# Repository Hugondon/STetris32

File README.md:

# STetris32
My version of the famous game "Tetris" using a system based on the Blue Pill dev board.
## Information
The sole purpose of this project is to recreate the game mechanics and introduce some other different features regarding in-game audio :). 
## Block Diagram

The system can be summarized in three big modules:
1. Game Display Module.
    - SPI communication with MAX7219 to control two 8x8 LED matrices.
    - I2C communication with SSD1306 OLED Driver connected to 128x64 dot display to show the player's score and the current song being played.
2. Sound Module.
    - PWM + NPN BJT circuit driven 4 ohm speakers.
3. User Interface Module.
    - 6 buttons with different functionalities (up/down/left/right/center/reset).
## Schematic
The connections the user must make are the following:

## Video

Pending upload.

## Useful Information
- [OLED Display](https://controllerstech.com/oled-display-using-i2c-stm32/)
- [Matrices](https://acoptex.com/project/160/basics-project-032a-8x8-dot-led-matrix-64-led-digital-display-common-anode-and-common-cathode-at-lex-c/)

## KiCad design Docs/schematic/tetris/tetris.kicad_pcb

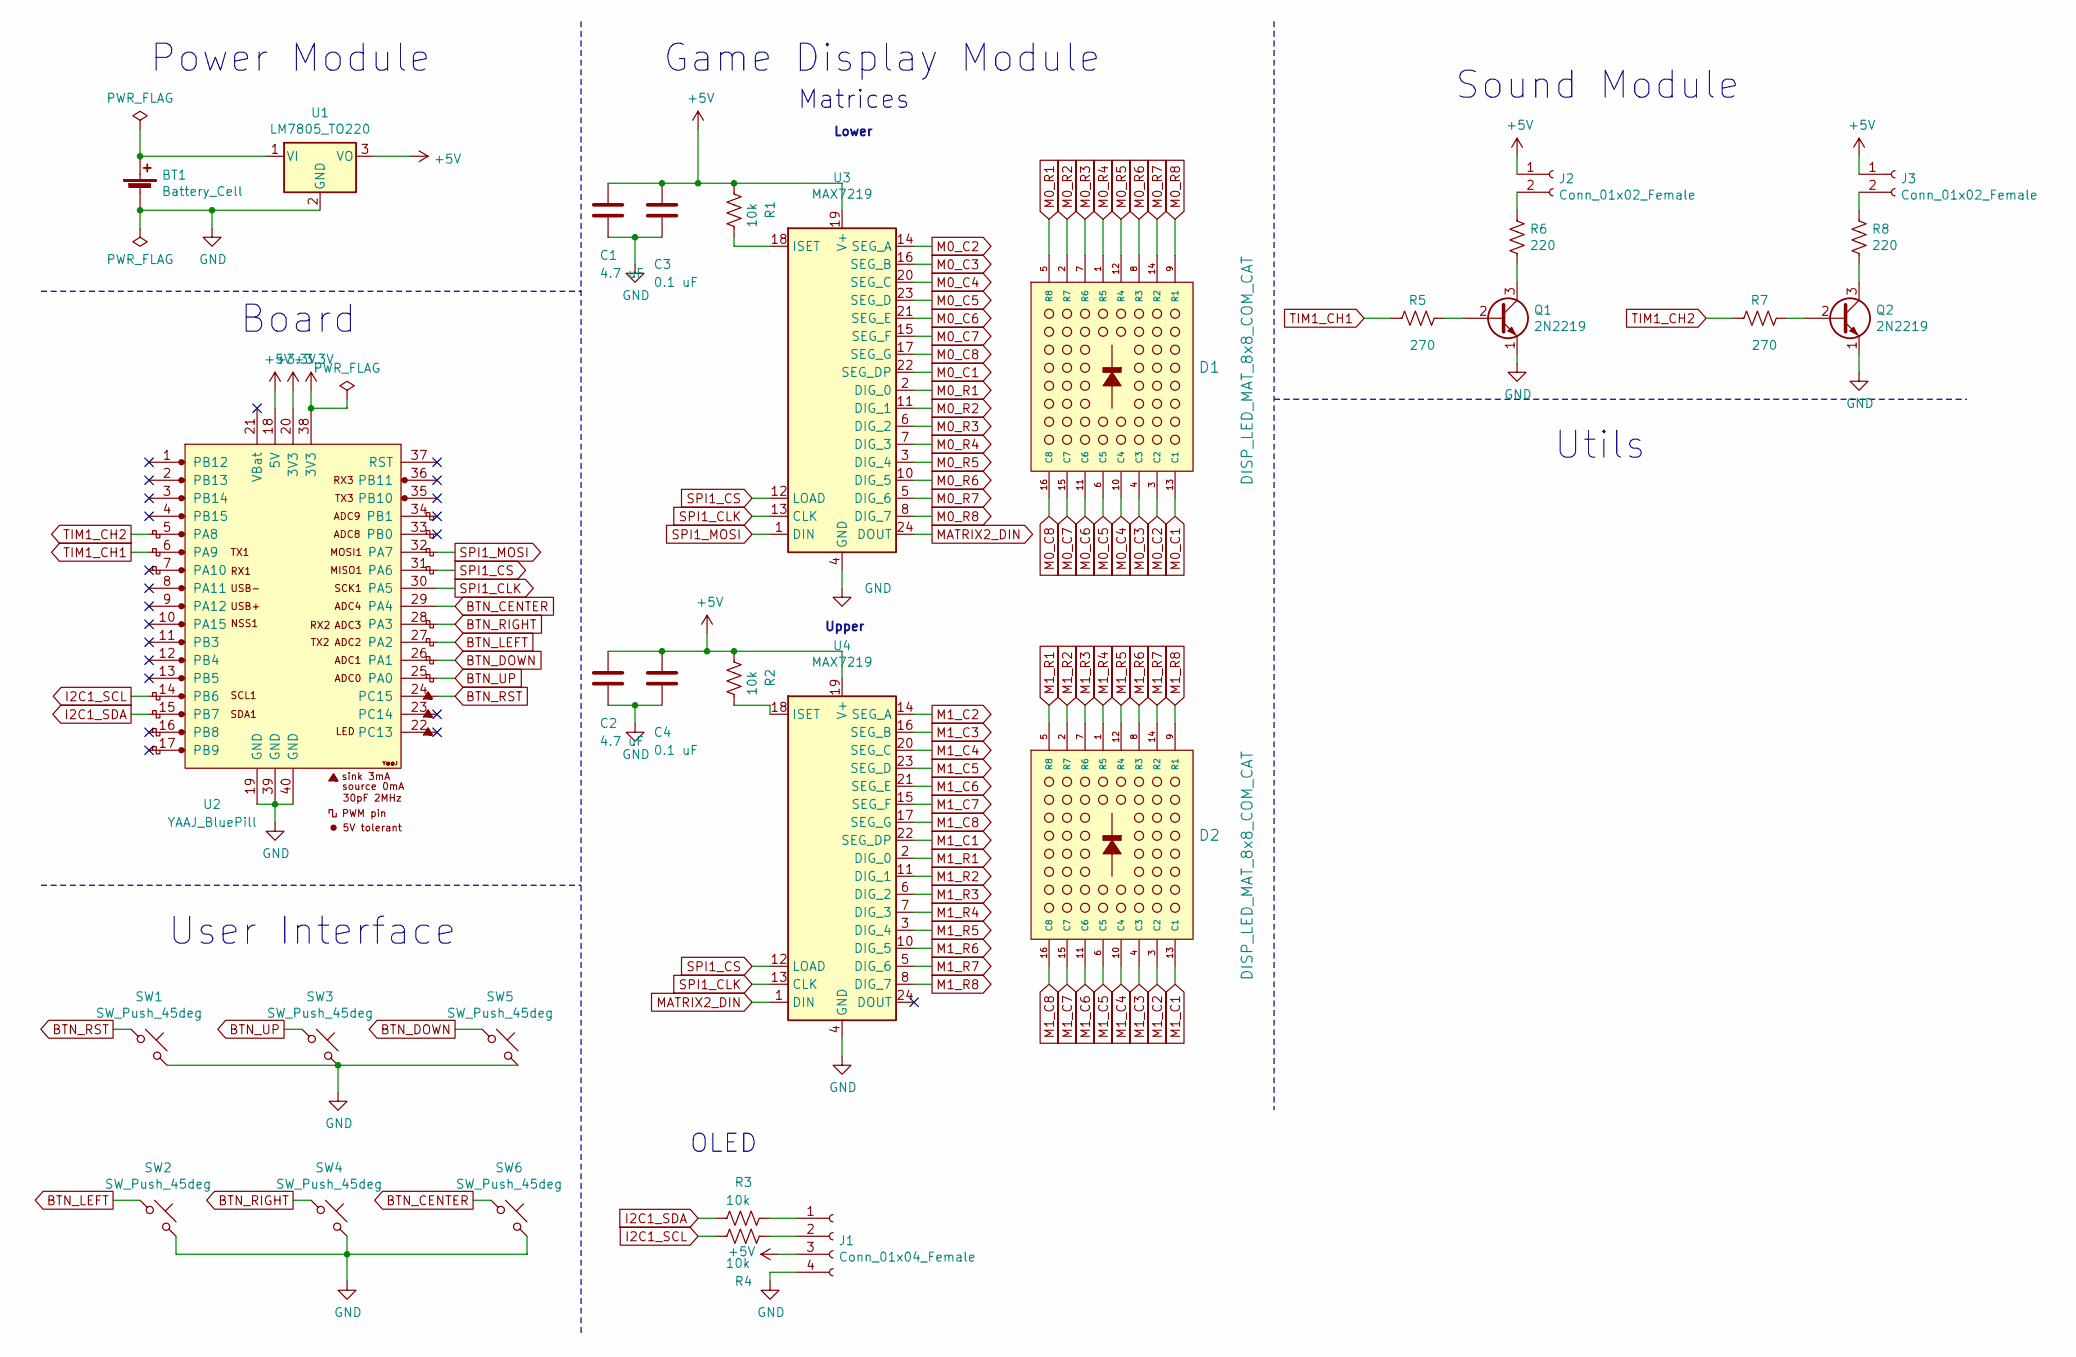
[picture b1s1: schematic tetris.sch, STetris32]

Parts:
BT1: Battery_Cell; BatteryHolder_MPD_BA9VPC_1xPP3
C1, C2: 4.7 uF; C_0603_1608Metric
C3, C4: 0.1 uF; C_0603_1608Metric
D1, D2: DISP_LED_MAT_8x8_COM_CAT; LED_8x8_3MM_32x32MM
J1: Conn_01x04_Female; PinHeader_1x04_P2.54mm_Vertical
J2, J3: Conn_01x02_Female; PinHeader_1x02_P2.54mm_Vertical
Q1, Q2: 2N2219; TO-92
R1, R2, R3, R4: 10k; R_0603_1608Metric
R5, R7: 270; R_0603_1608Metric
R6, R8: 220; R_0603_1608Metric
SW1, SW2, SW3, SW4, SW5, SW6: SW_Push_45deg; SW_PUSH-12mm
U1: LM7805_TO220; TO-220-3_Vertical
U2: YAAJ_BluePill; YAAJ_BluePill_1
U3, U4: MAX7219; DIP-24_W7.62mm

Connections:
+3V3: U2.20 (3V3), U2.38 (3V3)
+5V: C1.1, C2.1, C3.1, C4.1, J1.3, J2.1, J3.1, R1.1, R2.1, U1.3 (VO), U2.18 (5V), U3.19 (V+), U4.19 (V+)
BTN_CENTER: SW6.1, U2.29 (PA4)
BTN_DOWN: SW5.1, U2.26 (PA1)
BTN_LEFT: SW2.1, U2.27 (PA2)
BTN_RIGHT: SW4.1, U2.28 (PA3)
BTN_RST: SW1.1, U2.24 (PC15)
BTN_UP: SW3.1, U2.25 (PA0)
GND: BT1.2 (-), C1.2, C2.2, C3.2, C4.2, J1.4, Q1.1 (E), Q2.1 (E), SW1.2, SW2.2, SW3.2, SW4.2, SW5.2, SW6.2, U1.2 (GND), U2.19 (GND), U2.39 (GND), U2.40 (GND), U3.4 (GND), U3.9 (GND), U4.4 (GND), U4.9 (GND)
I2C1_SCL: R4.2, U2.14 (PB6)
I2C1_SDA: R3.2, U2.15 (PB7)
M0_C1: D1.13 (C1), U3.22 (SEG_DP)
M0_C2: D1.3 (C2), U3.14 (SEG_A)
M0_C3: D1.4 (C3), U3.16 (SEG_B)
M0_C4: D1.10 (C4), U3.20 (SEG_C)
M0_C5: D1.6 (C5), U3.23 (SEG_D)
M0_C6: D1.11 (C6), U3.21 (SEG_E)
M0_C7: D1.15 (C7), U3.15 (SEG_F)
M0_C8: D1.16 (C8), U3.17 (SEG_G)
M0_R1: D1.5 (R8), U3.2 (DIG_0)
M0_R2: D1.2 (R7), U3.11 (DIG_1)
M0_R3: D1.7 (R6), U3.6 (DIG_2)
M0_R4: D1.1 (R5), U3.7 (DIG_3)
M0_R5: D1.12 (R4), U3.3 (DIG_4)
M0_R6: D1.8 (R3), U3.10 (DIG_5)
M0_R7: D1.14 (R2), U3.5 (DIG_6)
M0_R8: D1.9 (R1), U3.8 (DIG_7)
M1_C1: D2.13 (C1), U4.22 (SEG_DP)
M1_C2: D2.3 (C2), U4.14 (SEG_A)
M1_C3: D2.4 (C3), U4.16 (SEG_B)
M1_C4: D2.10 (C4), U4.20 (SEG_C)
M1_C5: D2.6 (C5), U4.23 (SEG_D)
M1_C6: D2.11 (C6), U4.21 (SEG_E)
M1_C7: D2.15 (C7), U4.15 (SEG_F)
M1_C8: D2.16 (C8), U4.17 (SEG_G)
M1_R1: D2.5 (R8), U4.2 (DIG_0)
M1_R2: D2.2 (R7), U4.11 (DIG_1)
M1_R3: D2.7 (R6), U4.6 (DIG_2)
M1_R4: D2.1 (R5), U4.7 (DIG_3)
M1_R5: D2.12 (R4), U4.3 (DIG_4)
M1_R6: D2.8 (R3), U4.10 (DIG_5)
M1_R7: D2.14 (R2), U4.5 (DIG_6)
M1_R8: D2.9 (R1), U4.8 (DIG_7)
MATRIX2_DIN: U3.24 (DOUT), U4.1 (DIN)
unnamed: BT1.1 (+), U1.1 (VI)
unnamed: J1.1, R3.1
unnamed: J1.2, R4.1
unnamed: J2.2, R6.1
unnamed: J3.2, R8.1
unnamed: Q1.2 (B), R5.2
unnamed: Q1.3 (C), R6.2
unnamed: Q2.2 (B), R7.2
unnamed: Q2.3 (C), R8.2
unnamed: R1.2, U3.18 (ISET)
unnamed: R2.2, U4.18 (ISET)
SPI1_CLK: U2.30 (PA5), U3.13 (CLK), U4.13 (CLK)
SPI1_CS: U2.31 (PA6), U3.12 (LOAD), U4.12 (LOAD)
SPI1_MOSI: U2.32 (PA7), U3.1 (DIN)
TIM1_CH1: R5.1, U2.6 (PA9)
TIM1_CH2: R7.1, U2.5 (PA8)

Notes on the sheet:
Power Module
Board
User Interface
Game Display Module
Sound Module
Matrices
OLED
Utils
Lower
Upper

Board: 2 copper layers, 30 parts (0 on the bottom side), 60 nets, no tracks yet.

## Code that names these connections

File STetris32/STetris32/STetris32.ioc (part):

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Mcu.Name=STM32F103C(8-B)Tx
Mcu.Package=LQFP48
Mcu.UserName=STM32F103C8Tx
PA0-WKUP.GPIOParameters=GPIO_PuPd,GPIO_Label,GPIO_ModeDefaultEXTI
PA0-WKUP.GPIO_Label=BTN_UP
PA0-WKUP.GPIO_ModeDefaultEXTI=GPIO_MODE_IT_FALLING
PA0-WKUP.GPIO_PuPd=GPIO_PULLUP
PA0-WKUP.Signal=GPXTI0
PA1.GPIOParameters=GPIO_PuPd,GPIO_Label,GPIO_ModeDefaultEXTI
PA1.GPIO_Label=BTN_DOWN
PA1.GPIO_ModeDefaultEXTI=GPIO_MODE_IT_FALLING
PA1.GPIO_PuPd=GPIO_PULLUP
PA1.Signal=GPXTI1
PA13.Mode=Serial_Wire
PA13.Signal=SYS_JTMS-SWDIO
PA14.Mode=Serial_Wire
PA14.Signal=SYS_JTCK-SWCLK
PA2.GPIOParameters=GPIO_PuPd,GPIO_Label,GPIO_ModeDefaultEXTI
PA2.GPIO_Label=BTN_LEFT
PA2.GPIO_ModeDefaultEXTI=GPIO_MODE_IT_FALLING
PA2.GPIO_PuPd=GPIO_PULLUP
PA2.Signal=GPXTI2
PA3.GPIOParameters=GPIO_PuPd,GPIO_Label
PA3.GPIO_Label=BTN_RIGHT
PA3.GPIO_PuPd=GPIO_PULLUP
PA3.Signal=GPXTI3
PA4.GPIOParameters=GPIO_PuPd,GPIO_Label,GPIO_ModeDefaultEXTI
PA4.GPIO_Label=BTN_CENTER
PA4.GPIO_ModeDefaultEXTI=GPIO_MODE_IT_FALLING
PA4.GPIO_PuPd=GPIO_PULLUP
PA4.Signal=GPXTI4
PA5.Mode=TX_Only_Simplex_Unidirect_Master
PA5.Signal=SPI1_SCK
PA6.GPIOParameters=GPIO_Label
PA6.GPIO_Label=SPI1_CS
PA6.Signal=GPIO_Output
PA7.Mode=TX_Only_Simplex_Unidirect_Master
PA7.Signal=SPI1_MOSI
PA8.Signal=S_TIM1_CH1
PA9.Signal=S_TIM1_CH2
PB6.Mode=I2C
PB6.Signal=I2C1_SCL
PB7.Mode=I2C
PB7.Signal=I2C1_SDA
PC13-TAMPER-RTC.GPIOParameters=GPIO_Label
PC13-TAMPER-RTC.GPIO_Label=LED_BUILTIN
PC13-TAMPER-RTC.Signal=GPIO_Output
PC15-OSC32_OUT.GPIOParameters=GPIO_PuPd,GPIO_Label,GPIO_ModeDefaultEXTI
PC15-OSC32_OUT.GPIO_Label=BTN_RST
PC15-OSC32_OUT.GPIO_ModeDefaultEXTI=GPIO_MODE_IT_FALLING
PC15-OSC32_OUT.GPIO_PuPd=GPIO_PULLUP
PC15-OSC32_OUT.Signal=GPXTI15
PD0-OSC_IN.Mode=HSE-External-Oscillator
PD0-OSC_IN.Signal=RCC_OSC_IN
PD1-OSC_OUT.Mode=HSE-External-Oscillator
PD1-OSC_OUT.Signal=RCC_OSC_OUT
RCC.SYSCLKFreq_VALUE=16000000
RCC.SYSCLKSource=RCC_SYSCLKSOURCE_PLLCLK
board=custom

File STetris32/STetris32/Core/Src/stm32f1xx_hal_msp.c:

/* USER CODE BEGIN Header */
/**
  ******************************************************************************
  * File Name          : stm32f1xx_hal_msp.c
  * Description        : This file provides code for the MSP Initialization
  *                      and de-Initialization codes.
  ******************************************************************************
  * @attention
  *
  * <h2><center>&copy; Copyright (c) 2021 STMicroelectronics.
  * All rights reserved.</center></h2>
  *
  * This software component is licensed by ST under BSD 3-Clause license,
  * the "License"; You may not use this file except in compliance with the
  * License. You may obtain a copy of the License at:
  *                        opensource.org/licenses/BSD-3-Clause
  *
  ******************************************************************************
  */
/* USER CODE END Header */

/* Includes ------------------------------------------------------------------*/
#include "main.h"
/* USER CODE BEGIN Includes */

/* USER CODE END Includes */

/* Private typedef -----------------------------------------------------------*/
/* USER CODE BEGIN TD */

/* USER CODE END TD */

/* Private define ------------------------------------------------------------*/
/* USER CODE BEGIN Define */

/* USER CODE END Define */

/* Private macro -------------------------------------------------------------*/
/* USER CODE BEGIN Macro */

/* USER CODE END Macro */

/* Private variables ---------------------------------------------------------*/
/* USER CODE BEGIN PV */

/* USER CODE END PV */

/* Private function prototypes -----------------------------------------------*/
/* USER CODE BEGIN PFP */

/* USER CODE END PFP */

/* External functions --------------------------------------------------------*/
/* USER CODE BEGIN ExternalFunctions */

/* USER CODE END ExternalFunctions */

/* USER CODE BEGIN 0 */

/* USER CODE END 0 */

void HAL_TIM_MspPostInit(TIM_HandleTypeDef *htim);
                    /**
  * Initializes the Global MSP.
  */
void HAL_MspInit(void)
{
  /* USER CODE BEGIN MspInit 0 */

  /* USER CODE END MspInit 0 */

  __HAL_RCC_AFIO_CLK_ENABLE();
  __HAL_RCC_PWR_CLK_ENABLE();

  /* System interrupt init*/

  /** NOJTAG: JTAG-DP Disabled and SW-DP Enabled
  */
  __HAL_AFIO_REMAP_SWJ_NOJTAG();

  /* USER CODE BEGIN MspInit 1 */

  /* USER CODE END MspInit 1 */
}

/**
* @brief I2C MSP Initialization
* This function configures the hardware resources used in this example
* @param hi2c: I2C handle pointer
* @retval None
*/
void HAL_I2C_MspInit(I2C_HandleTypeDef* hi2c)
{
  GPIO_InitTypeDef GPIO_InitStruct = {0};
  if(hi2c->Instance==I2C1)
  {
  /* USER CODE BEGIN I2C1_MspInit 0 */

  /* USER CODE END I2C1_MspInit 0 */

    __HAL_RCC_GPIOB_CLK_ENABLE();
    /**I2C1 GPIO Configuration
    PB6     ------> I2C1_SCL
    PB7     ------> I2C1_SDA
    */
    GPIO_InitStruct.Pin = GPIO_PIN_6|GPIO_PIN_7;
    GPIO_InitStruct.Mode = GPIO_MODE_AF_OD;
    GPIO_InitStruct.Speed = GPIO_SPEED_FREQ_HIGH;
    HAL_GPIO_Init(GPIOB, &GPIO_InitStruct);

    /* Peripheral clock enable */
    __HAL_RCC_I2C1_CLK_ENABLE();
  /* USER CODE BEGIN I2C1_MspInit 1 */

  /* USER CODE END I2C1_MspInit 1 */
  }

}

/**
* @brief I2C MSP De-Initialization
* This function freeze the hardware resources used in this example
* @param hi2c: I2C handle pointer
* @retval None
*/
void HAL_I2C_MspDeInit(I2C_HandleTypeDef* hi2c)
{
  if(hi2c->Instance==I2C1)
  {
  /* USER CODE BEGIN I2C1_MspDeInit 0 */

  /* USER CODE END I2C1_MspDeInit 0 */
    /* Peripheral clock disable */
    __HAL_RCC_I2C1_CLK_DISABLE();

    /**I2C1 GPIO Configuration
    PB6     ------> I2C1_SCL
    PB7     ------> I2C1_SDA
    */
    HAL_GPIO_DeInit(GPIOB, GPIO_PIN_6);

    HAL_GPIO_DeInit(GPIOB, GPIO_PIN_7);

  /* USER CODE BEGIN I2C1_MspDeInit 1 */

  /* USER CODE END I2C1_MspDeInit 1 */
  }

}

/**
* @brief SPI MSP Initialization
* This function configures the hardware resources used in this example
* @param hspi: SPI handle pointer
* @retval None
*/
void HAL_SPI_MspInit(SPI_HandleTypeDef* hspi)
{
  GPIO_InitTypeDef GPIO_InitStruct = {0};
  if(hspi->Instance==SPI1)
  {
  /* USER CODE BEGIN SPI1_MspInit 0 */

  /* USER CODE END SPI1_MspInit 0 */
    /* Peripheral clock enable */
    __HAL_RCC_SPI1_CLK_ENABLE();

    __HAL_RCC_GPIOA_CLK_ENABLE();
    /**SPI1 GPIO Configuration
    PA5     ------> SPI1_SCK
    PA7     ------> SPI1_MOSI
    */
    GPIO_InitStruct.Pin = GPIO_PIN_5|GPIO_PIN_7;
    GPIO_InitStruct.Mode = GPIO_MODE_AF_PP;
    GPIO_InitStruct.Speed = GPIO_SPEED_FREQ_HIGH;
    HAL_GPIO_Init(GPIOA, &GPIO_InitStruct);

  /* USER CODE BEGIN SPI1_MspInit 1 */

  /* USER CODE END SPI1_MspInit 1 */
  }

}

/**
* @brief SPI MSP De-Initialization
* This function freeze the hardware resources used in this example
* @param hspi: SPI handle pointer
* @retval None
*/
void HAL_SPI_MspDeInit(SPI_HandleTypeDef* hspi)
{
  if(hspi->Instance==SPI1)
  {
  /* USER CODE BEGIN SPI1_MspDeInit 0 */

  /* USER CODE END SPI1_MspDeInit 0 */
    /* Peripheral clock disable */
    __HAL_RCC_SPI1_CLK_DISABLE();

    /**SPI1 GPIO Configuration
    PA5     ------> SPI1_SCK
    PA7     ------> SPI1_MOSI
    */
    HAL_GPIO_DeInit(GPIOA, GPIO_PIN_5|GPIO_PIN_7);

  /* USER CODE BEGIN SPI1_MspDeInit 1 */

  /* USER CODE END SPI1_MspDeInit 1 */
  }

}

/**
* @brief TIM_OC MSP Initialization
* This function configures the hardware resources used in this example
* @param htim_oc: TIM_OC handle pointer
* @retval None
*/
void HAL_TIM_OC_MspInit(TIM_HandleTypeDef* htim_oc)
{
  if(htim_oc->Instance==TIM1)
  {
  /* USER CODE BEGIN TIM1_MspInit 0 */

  /* USER CODE END TIM1_MspInit 0 */
    /* Peripheral clock enable */
    __HAL_RCC_TIM1_CLK_ENABLE();
  /* USER CODE BEGIN TIM1_MspInit 1 */

  /* USER CODE END TIM1_MspInit 1 */
  }

}

/**
* @brief TIM_Base MSP Initialization
* This function configures the hardware resources used in this example
* @param htim_base: TIM_Base handle pointer
* @retval None
*/
void HAL_TIM_Base_MspInit(TIM_HandleTypeDef* htim_base)
{
  if(htim_base->Instance==TIM2)
  {
  /* USER CODE BEGIN TIM2_MspInit 0 */

  /* USER CODE END TIM2_MspInit 0 */
    /* Peripheral clock enable */
    __HAL_RCC_TIM2_CLK_ENABLE();
    /* TIM2 interrupt Init */
    HAL_NVIC_SetPriority(TIM2_IRQn, 0, 0);
    HAL_NVIC_EnableIRQ(TIM2_IRQn);
  /* USER CODE BEGIN TIM2_MspInit 1 */

  /* USER CODE END TIM2_MspInit 1 */
  }
  else if(htim_base->Instance==TIM3)
  {
  /* USER CODE BEGIN TIM3_MspInit 0 */

  /* USER CODE END TIM3_MspInit 0 */
    /* Peripheral clock enable */
    __HAL_RCC_TIM3_CLK_ENABLE();
    /* TIM3 interrupt Init */
    HAL_NVIC_SetPriority(TIM3_IRQn, 0, 0);
    HAL_NVIC_EnableIRQ(TIM3_IRQn);
  /* USER CODE BEGIN TIM3_MspInit 1 */

  /* USER CODE END TIM3_MspInit 1 */
  }

}

void HAL_TIM_MspPostInit(TIM_HandleTypeDef* htim)
{
  GPIO_InitTypeDef GPIO_InitStruct = {0};
  if(htim->Instance==TIM1)
  {
  /* USER CODE BEGIN TIM1_MspPostInit 0 */

  /* USER CODE END TIM1_MspPostInit 0 */

    __HAL_RCC_GPIOA_CLK_ENABLE();
    /**TIM1 GPIO Configuration
    PA8     ------> TIM1_CH1
    PA9     ------> TIM1_CH2
    */
    GPIO_InitStruct.Pin = GPIO_PIN_8|GPIO_PIN_9;
    GPIO_InitStruct.Mode = GPIO_MODE_AF_PP;
    GPIO_InitStruct.Speed = GPIO_SPEED_FREQ_LOW;
    HAL_GPIO_Init(GPIOA, &GPIO_InitStruct);

  /* USER CODE BEGIN TIM1_MspPostInit 1 */

  /* USER CODE END TIM1_MspPostInit 1 */
  }

}
/**
* @brief TIM_OC MSP De-Initialization
* This function freeze the hardware resources used in this example
* @param htim_oc: TIM_OC handle pointer
* @retval None
*/
void HAL_TIM_OC_MspDeInit(TIM_HandleTypeDef* htim_oc)
{
  if(htim_oc->Instance==TIM1)
  {
  /* USER CODE BEGIN TIM1_MspDeInit 0 */

  /* USER CODE END TIM1_MspDeInit 0 */
    /* Peripheral clock disable */
    __HAL_RCC_TIM1_CLK_DISABLE();
  /* USER CODE BEGIN TIM1_MspDeInit 1 */

  /* USER CODE END TIM1_MspDeInit 1 */
  }

}

/**
* @brief TIM_Base MSP De-Initialization
* This function freeze the hardware resources used in this example
* @param htim_base: TIM_Base handle pointer
* @retval None
*/
void HAL_TIM_Base_MspDeInit(TIM_HandleTypeDef* htim_base)
{
  if(htim_base->Instance==TIM2)
  {
  /* USER CODE BEGIN TIM2_MspDeInit 0 */

  /* USER CODE END TIM2_MspDeInit 0 */
    /* Peripheral clock disable */
    __HAL_RCC_TIM2_CLK_DISABLE();

    /* TIM2 interrupt DeInit */
    HAL_NVIC_DisableIRQ(TIM2_IRQn);
  /* USER CODE BEGIN TIM2_MspDeInit 1 */

  /* USER CODE END TIM2_MspDeInit 1 */
  }
  else if(htim_base->Instance==TIM3)
  {
  /* USER CODE BEGIN TIM3_MspDeInit 0 */

  /* USER CODE END TIM3_MspDeInit 0 */
    /* Peripheral clock disable */
    __HAL_RCC_TIM3_CLK_DISABLE();

    /* TIM3 interrupt DeInit */
    HAL_NVIC_DisableIRQ(TIM3_IRQn);
  /* USER CODE BEGIN TIM3_MspDeInit 1 */

  /* USER CODE END TIM3_MspDeInit 1 */
  }

}

/* USER CODE BEGIN 1 */

/* USER CODE END 1 */

/************************ (C) COPYRIGHT STMicroelectronics *****END OF FILE****/

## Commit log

2021-02-08 Resized block diagram
2021-02-08 Fix block diagram
2021-02-08 block diagram fix
2021-02-11 added matrix functionality
2021-02-11 examples and buffers added
2021-02-11 array test added
2021-02-12 added I2C display functionality
2021-02-12 added external interrupts + debouncing for buttons
2021-02-12 added stm32f103c8t6 datasheet
2021-02-12 debounce fix
2021-02-12 score modification added
2021-02-13 added tests for pieces movement
2021-02-13 added movement through interrupts + shift func
2021-02-15 changed main menu
2021-02-22 added sound module tone generator
2021-02-22 added HAL documentation
2021-02-22 added sound module with speakers to main
2021-02-22 updated block diagram
2021-02-22 added note durations and second PWM
2021-02-24 added image of protoboard circuit
2021-02-27 added schematic
2021-02-27 added schematic png
2021-02-27 LED matrix fix
2021-03-07 akn-kicad-libs matrix fix
2021-03-31 el coco es mi novio
2021-05-03 Functions refactor
